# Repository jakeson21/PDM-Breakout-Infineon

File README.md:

# PDM-Breakout-Infineon
Breakout board for Infineon IM69D128SV, IM72D128V and IM73D128V

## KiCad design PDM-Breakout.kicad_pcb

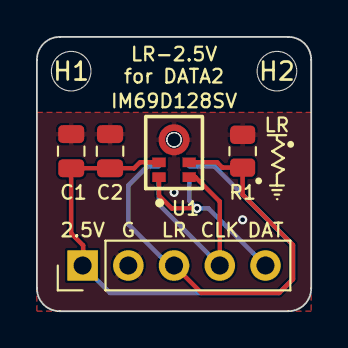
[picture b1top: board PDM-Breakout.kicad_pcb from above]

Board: 4 copper layers, 15.2 x 15.2 mm, 8 parts (1 on the bottom side), 5 nets.

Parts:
C1: 10uF; C_0805_2012Metric
C2: 0.1uF; C_0805_2012Metric
H1, H2: M2; MountingHole_2.2mm_M2
J1: Conn_01x05; PinHeader_1x05_P2.54mm_Vertical
R1: 10K; R_0805_2012Metric
U1: IM69D128SV; IFX-PG-LLGA-5-4_IM69D128
U2: IM72D128V; IFX-PG-LLGA-5-4

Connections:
/CLOCK: J1.4, U1.3 (CLOCK), U2.3 (CLOCK)
/DATA: J1.5, U1.1 (DATA), U2.1 (DATA)
/LR: J1.3, R1.1, U1.4 (LR), U2.4 (LR)
GND: C1.2, C2.2, J1.2, R1.2, U1.5 (GND), U2.5 (GND)
VDD: C1.1, C2.1, J1.1, U1.2 (VDD), U2.2 (VDD)

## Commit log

2025-08-31 v1.0 sent to fab 2025/08/30
